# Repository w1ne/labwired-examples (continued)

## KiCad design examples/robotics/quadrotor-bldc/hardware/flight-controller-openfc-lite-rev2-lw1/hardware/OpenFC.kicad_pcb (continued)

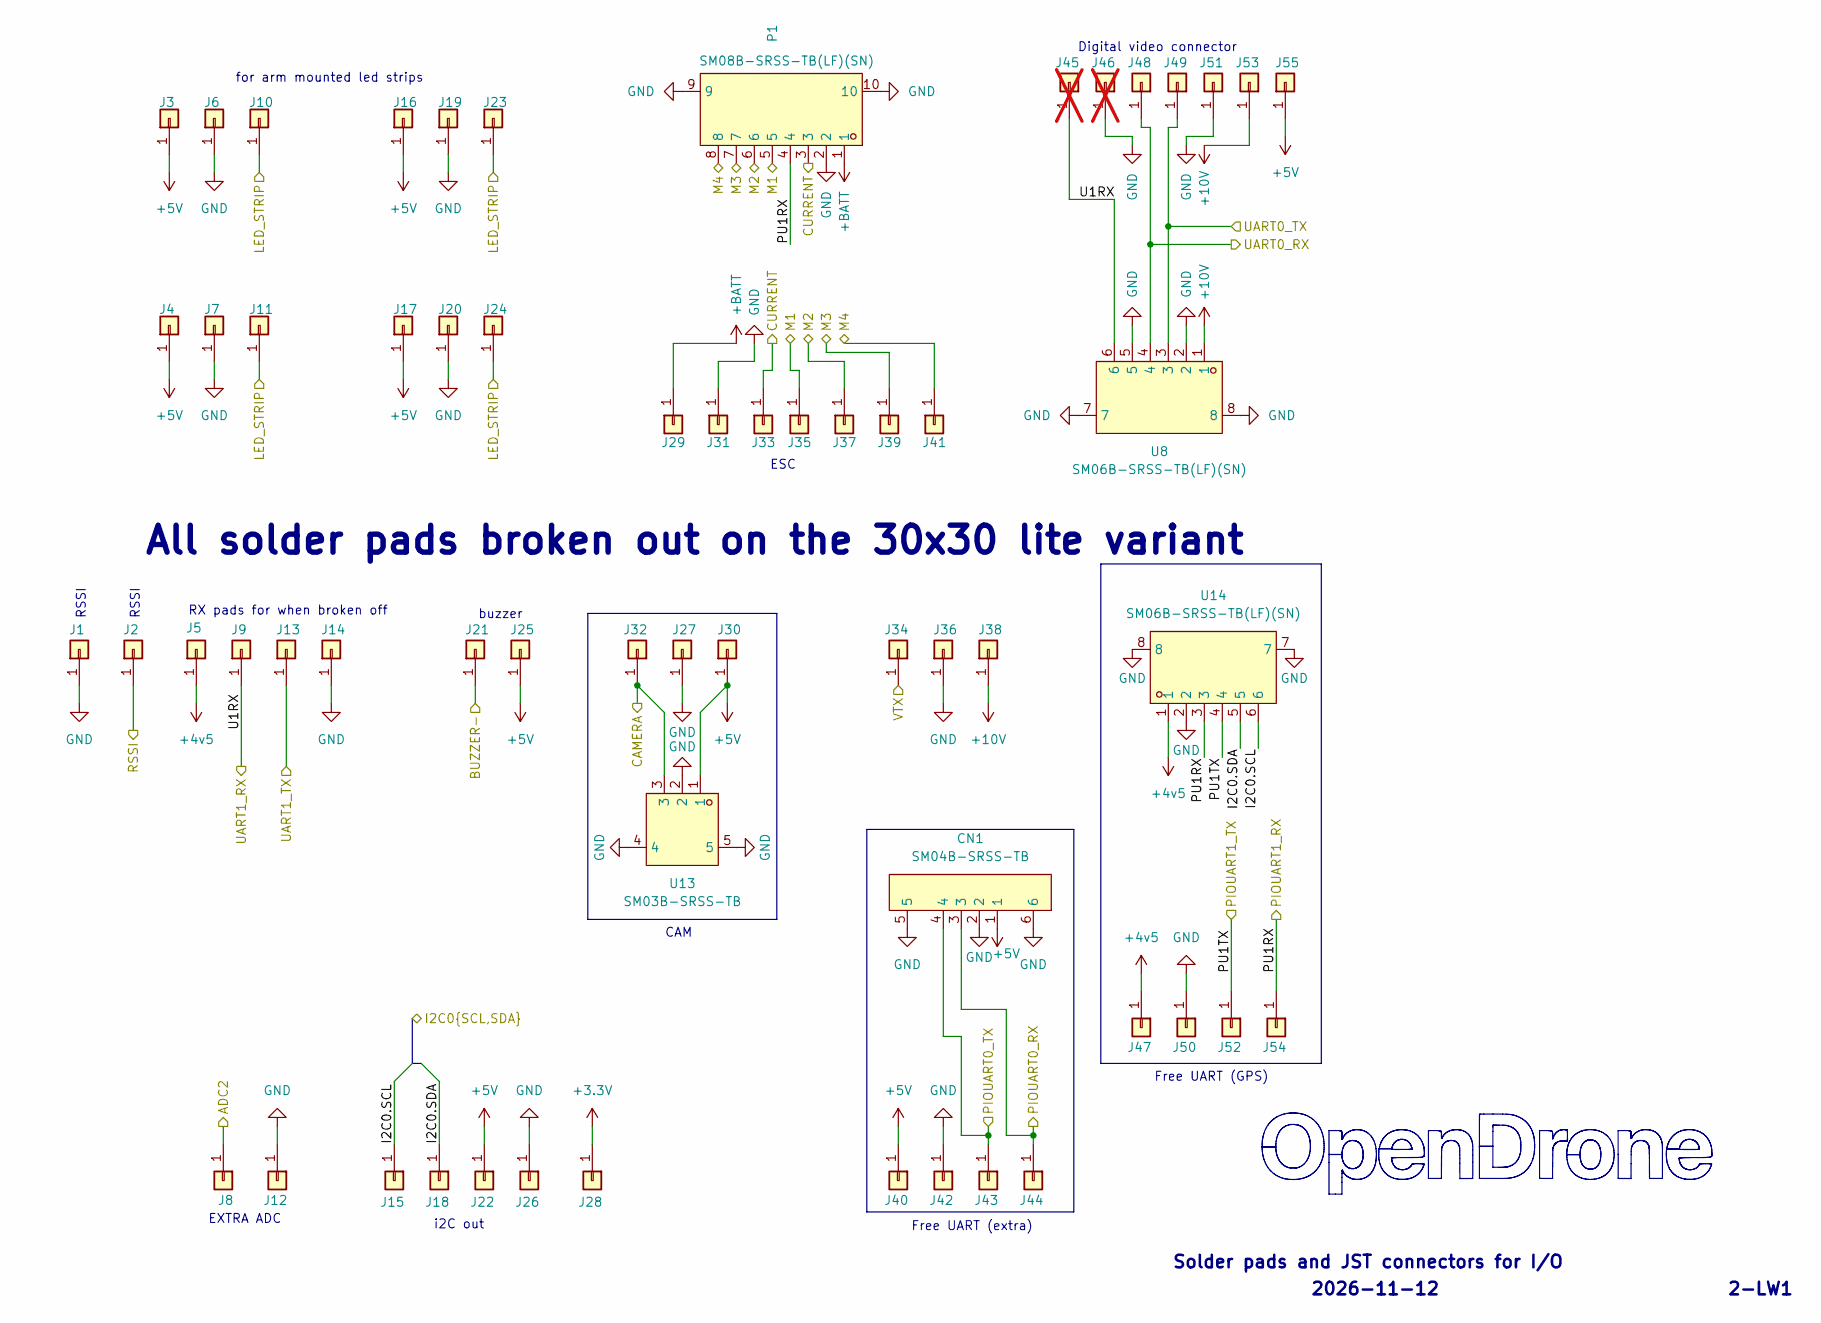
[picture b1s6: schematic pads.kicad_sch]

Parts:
CN1: SM04B-SRSS-TB; CONN-SMD_4P-P1.00_SM04B-SRSS-TB-LF-SN; MPN SM04B-SRSS-TB(LF)(SN); LCSC C160404
J1, J2, J3, J4, J5, J6, J7, J8, J9, J10, J11, J12, J13, J14, J15, J16, J17, J18, J19, J20, J21, J22, J23, J24, J25, J26, J27, J28, J29, J30, J31, J32, J33, J34, J35, J36, J37, J38, J39, J40, J41, J42, J43, J44, J47, J48, J49, J50, J51, J52, J53, J54, J55: 5V; small_pad
J45, J46: 5V; small_pad; not fitted
P1: SM08B-SRSS-TB(LF)(SN); CONN-TH_SM08B-SRSS-TB-LF-SN; MPN SM08B-SRSS-TB(LF)(SN); LCSC C160407
U8, U14: SM06B-SRSS-TB(LF)(SN); CONN-SMD_SM06B-SRSS-TB-LF-SN; MPN SM06B-SRSS-TB(LF)(SN); LCSC C160405
U13: SM03B-SRSS-TB; CONN-SMD_SM03B-SRSS-TB-LF-SN-P; MPN SM03B-SRSS-TB(LF)(SN); LCSC C160403

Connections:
+3.3V: J28.1 (Pin_1_1); also elsewhere on the board
+4v5: J5.1 (Pin_1_1), J47.1 (Pin_1_1), U14.1; also elsewhere on the board
+5V: CN1.1, J3.1 (Pin_1_1), J4.1 (Pin_1_1), J16.1 (Pin_1_1), J17.1 (Pin_1_1), J22.1 (Pin_1_1), J25.1 (Pin_1_1), J30.1 (Pin_1_1), J40.1 (Pin_1_1), J55.1 (Pin_1_1), U13.1; also elsewhere on the board
+10V: J38.1 (Pin_1_1), J53.1 (Pin_1_1), U8.1; also elsewhere on the board
+BATT: J29.1 (Pin_1_1), P1.1; also elsewhere on the board
/OSD/VIDEO_IN: J32.1 (Pin_1_1), U13.3; also elsewhere on the board
/OSD/VIDEO_OUT: J34.1 (Pin_1_1); also elsewhere on the board
/PADS/ADC2: J8.1 (Pin_1_1); also elsewhere on the board
/PADS/BUZZER-: J21.1 (Pin_1_1); also elsewhere on the board
/PADS/CURRENT: J33.1 (Pin_1_1), P1.3; also elsewhere on the board
/PADS/I2C0.SCL: J15.1 (Pin_1_1), U14.6; also elsewhere on the board
/PADS/I2C0.SDA: J18.1 (Pin_1_1), U14.5; also elsewhere on the board
/PADS/LED_STRIP: J10.1 (Pin_1_1), J11.1 (Pin_1_1), J23.1 (Pin_1_1), J24.1 (Pin_1_1); also elsewhere on the board
/PADS/M1: J35.1 (Pin_1_1), P1.5; also elsewhere on the board
/PADS/M2: J37.1 (Pin_1_1), P1.6; also elsewhere on the board
/PADS/M3: J39.1 (Pin_1_1), P1.7; also elsewhere on the board
/PADS/M4: J41.1 (Pin_1_1), P1.8; also elsewhere on the board
/PADS/PIOUART0_RX: CN1.3, J44.1 (Pin_1_1); also elsewhere on the board
/PADS/PIOUART0_TX: CN1.4, J43.1 (Pin_1_1); also elsewhere on the board
/PADS/PU1RX: J54.1 (Pin_1_1), P1.4, U14.3; also elsewhere on the board
/PADS/PU1TX: J52.1 (Pin_1_1), U14.4; also elsewhere on the board
/PADS/RSSI: J2.1 (Pin_1_1); also elsewhere on the board
/PADS/U1RX: J9.1 (Pin_1_1), J45.1, U8.6; also elsewhere on the board
/PADS/UART0_RX: J48.1 (Pin_1_1), U8.4; also elsewhere on the board
/PADS/UART0_TX: J49.1 (Pin_1_1), U8.3; also elsewhere on the board
/PADS/UART1_TX: J13.1 (Pin_1_1); also elsewhere on the board
GND: CN1.2, CN1.5, CN1.6, J1.1 (Pin_1_1), J6.1 (Pin_1_1), J7.1 (Pin_1_1), J12.1 (Pin_1_1), J14.1 (Pin_1_1), J19.1 (Pin_1_1), J20.1 (Pin_1_1), J26.1 (Pin_1_1), J27.1 (Pin_1_1), J31.1 (Pin_1_1), J36.1 (Pin_1_1), J42.1 (Pin_1_1), J46.1, J50.1 (Pin_1_1), J51.1 (Pin_1_1), P1.2, P1.9, P1.10, U8.2, U8.5, U8.7, U8.8, U13.2, U13.4, U13.5, U14.2, U14.7, U14.8; also elsewhere on the board

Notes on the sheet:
2026-11-12
RSSI
Free UART (extra)
Solder pads and JST connectors for I/O
i2C out
CAM
All solder pads broken out on the 30x30 lite variant
Free UART (GPS)
buzzer
2-LW1
RX pads for when broken off
ESC
Digital video connector
EXTRA ADC
for arm mounted led strips

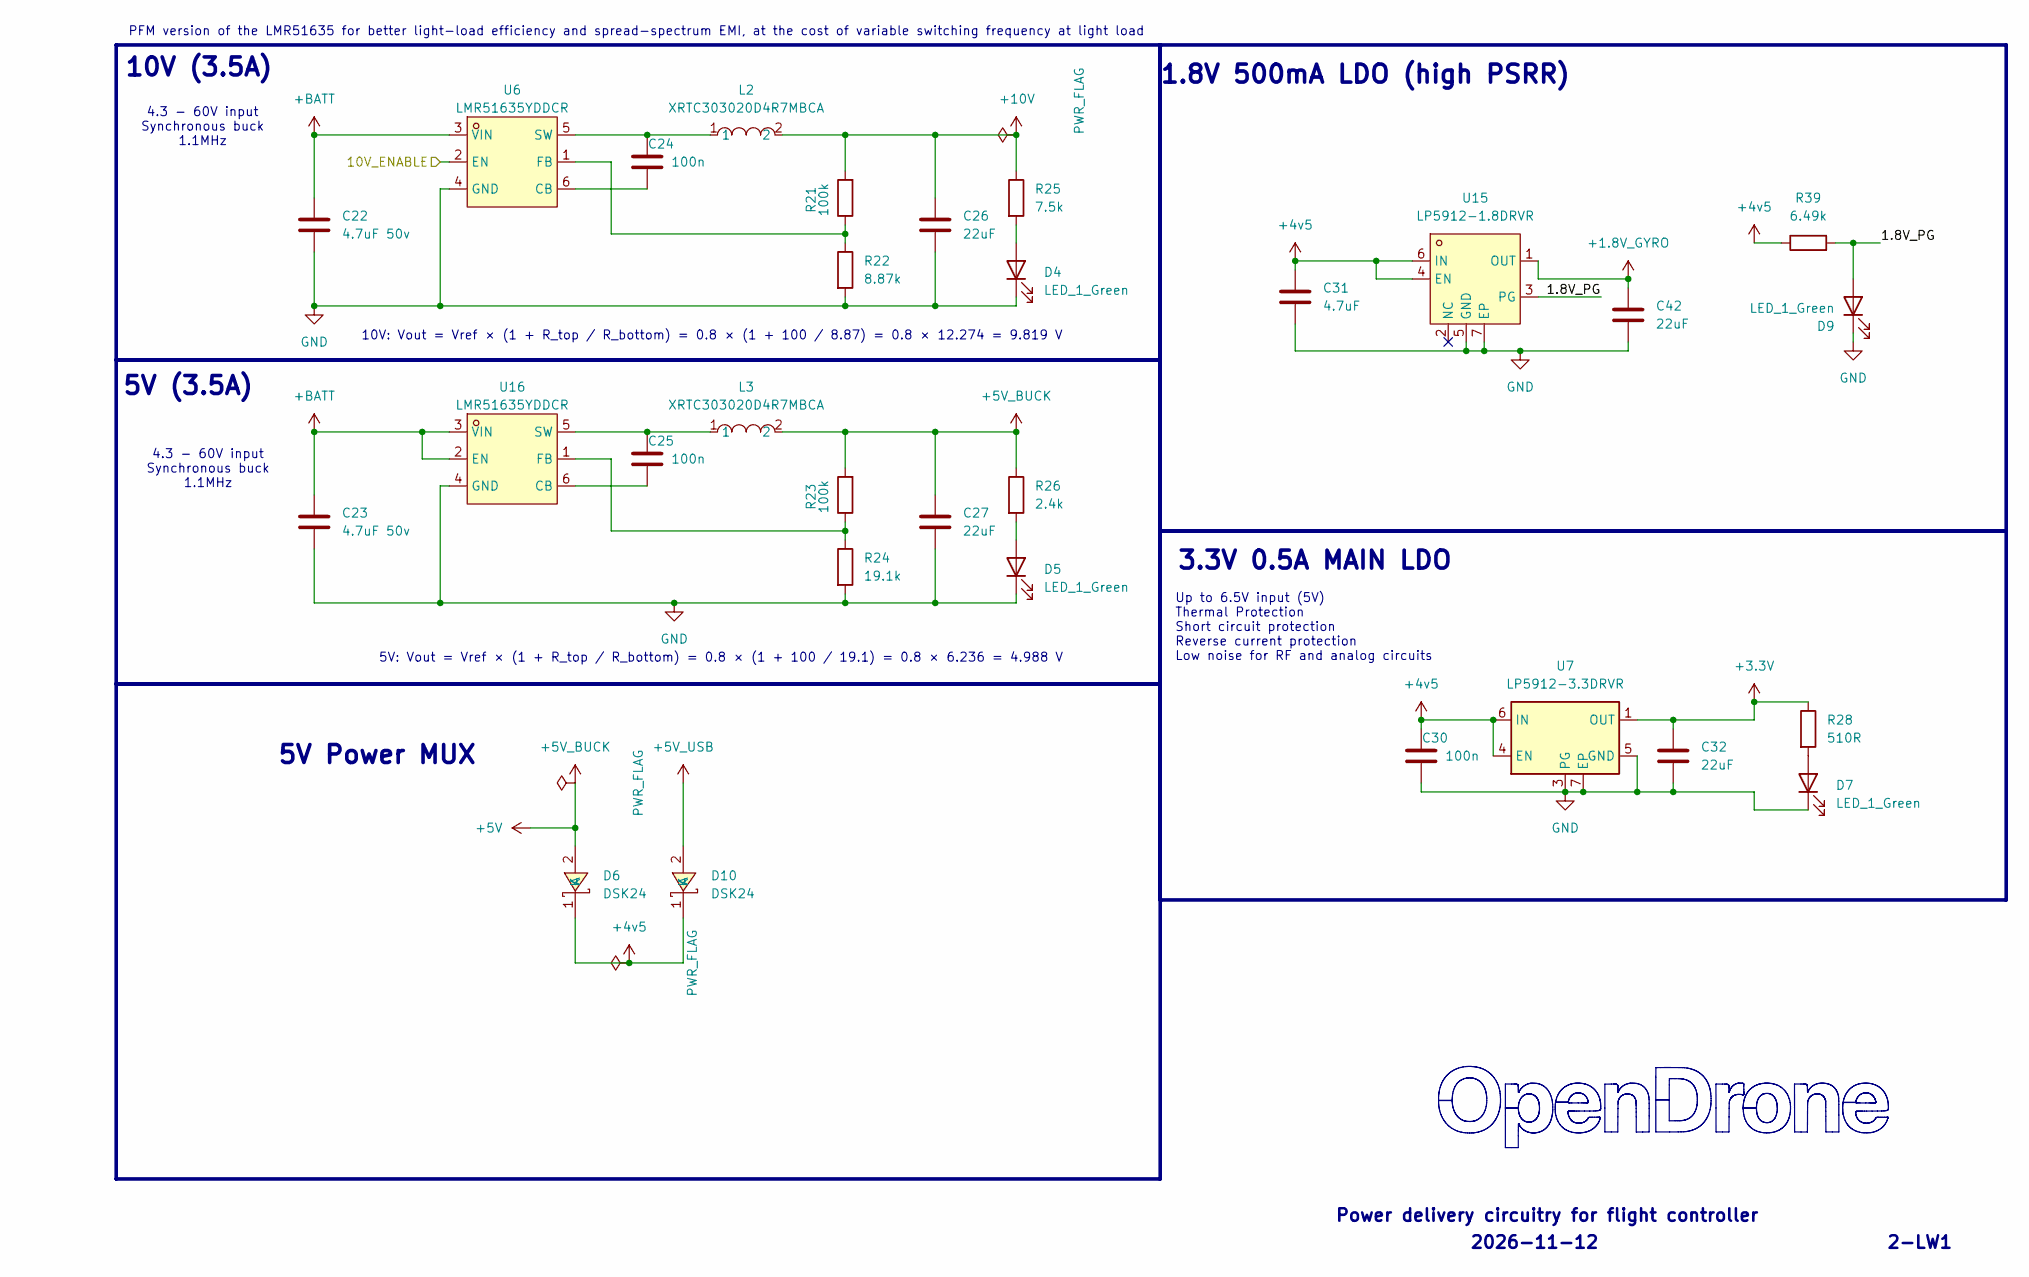
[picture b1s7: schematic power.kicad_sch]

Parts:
C22, C23: 4.7uF 50v; C_0805_2012Metric; MPN CL21A475KBQNNNE; LCSC C98192
C24, C25, C30: 100n; C_0201_0603Metric; MPN GRM033R61E104KE14D; LCSC C76939
C26, C27: 22uF; C_0603_1608Metric; MPN CL10A226MO7JZNC; LCSC C2762594
C31: 4.7uF; C_0402_1005Metric; MPN CL05A475MP5NRNC; LCSC C23733
C32: 22uF; C_0402_1005Metric; MPN CL05A226MQ5QUNC; LCSC C105226
C42: 22uF; C_0402_1005Metric; MPN GRM155R60J226ME11D; LCSC C415703
D4, D5, D7, D9: LED_1_Green; LED_0402_1005Metric; MPN XL-1005UGC; LCSC C965793
D6, D10: DSK24; SOD-123_L2.8-W1.8-LS3.7-RD; MPN DSK24; LCSC C64890
L2, L3: XRTC303020D4R7MBCA; IND-SMD_L3.0-W3.0_AFE303020S; MPN XRTC303020D4R7MBCA; LCSC C39846837
R21, R23: 100k; R_0201_0603Metric; MPN 0201WMF1003TEE; LCSC C270364
R22: 8.87k; R_0201_0603Metric; MPN RTT018871FTH; LCSC C332577
R24: 19.1k; R_0201_0603Metric; MPN RC-01W1912FT; LCSC C320741
R25: 7.5k; R_0201_0603Metric; MPN RC0201FR-077K5L; LCSC C474437
R26: 2.4k; R_0201_0603Metric; MPN RTT012401FTH; LCSC C166281
R28: 510R; R_0201_0603Metric; MPN RC0201FR-07510RL; LCSC C57784
R39: 6.49k; R_0201_0603Metric; MPN AF0201FR-076K49L; LCSC C2107920
U6, U16: LMR51635YDDCR; SOT-23-6_L2.9-W1.6-P0.95-LS2.8-BL; MPN LMR51635YDDCR; LCSC C45262770
U7: LP5912-3.3DRVR; WSON-6-1EP_2x2mm_P0.65mm_EP1x1.6mm; MPN LP5912-3.3DRVR; LCSC C524780
U15: LP5912-1.8DRVR; WSON-6-1EP_2x2mm_P0.65mm_EP1x1.6mm_ThermalVias; MPN LP5912-1.8DRVR; LCSC C2876234

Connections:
+1.8V_GYRO: C42.1, U15.1 (OUT); also elsewhere on the board
+3.3V: C32.1, R28.1, U7.1 (OUT); also elsewhere on the board
+4v5: C30.1, C31.1, D6.1 (K), D10.1 (K), R39.1, U7.4 (EN), U7.6 (IN), U15.4 (EN), U15.6 (IN); also elsewhere on the board
+5V: C27.1, D6.2 (A), L3.2, R23.2, R26.1; also elsewhere on the board
+5V_USB: D10.2 (A); also elsewhere on the board
+10V: C26.1, L2.2, R21.2, R25.1; also elsewhere on the board
+BATT: C22.1, C23.1, U6.3 (VIN), U16.2 (EN), U16.3 (VIN); also elsewhere on the board
/POWER/1.8V_PG: D9.2 (A), R39.2, U15.3 (PG)
/POWER/10V_ENABLE: U6.2 (EN); also elsewhere on the board
GND: C22.2, C23.2, C26.2, C27.2, C30.2, C31.2, C32.2, C42.2, D4.1 (K), D5.1 (K), D7.1 (K), D9.1 (K), R22.2, R24.2, U6.4 (GND), U7.3 (GND), U7.5 (PG), U7.7 (EP), U15.5 (GND), U15.7 (EP), U16.4 (GND); also elsewhere on the board
unnamed: D4.2 (A), R25.2
unnamed: D5.2 (A), R26.2
unnamed: D7.2 (A), R28.2
unnamed: C24.2, U6.6 (CB)
unnamed: R21.1, R22.1, U6.1 (FB)
unnamed: C24.1, L2.1, U6.5 (SW)
unnamed: C25.2, U16.6 (CB)
unnamed: R23.1, R24.1, U16.1 (FB)
unnamed: C25.1, L3.1, U16.5 (SW)

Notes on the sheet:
5V Power MUX
4.3 - 60V input Synchronous buck 1.1MHz
Power delivery circuitry for flight controller
2026-11-12
2-LW1
10V: Vout = Vref × (1 + R_top / R_bottom) = 0.8 × (1 + 100 / 8.87) = 0.8 × 12.274 = 9.819 V
5V: Vout = Vref × (1 + R_top / R_bottom) = 0.8 × (1 + 100 / 19.1) = 0.8 × 6.236 = 4.988 V
Up to 6.5V input (5V) Thermal Protection Short circuit protection Reverse current protection Low noise for RF and analog circuits
5V (3.5A)
1.8V 500mA LDO (high PSRR)
PFM version of the LMR51635 for better light-load efficiency and spread-spectrum EMI, at the cost of variable switching frequency at light load
10V (3.5A)
3.3V 0.5A MAIN LDO

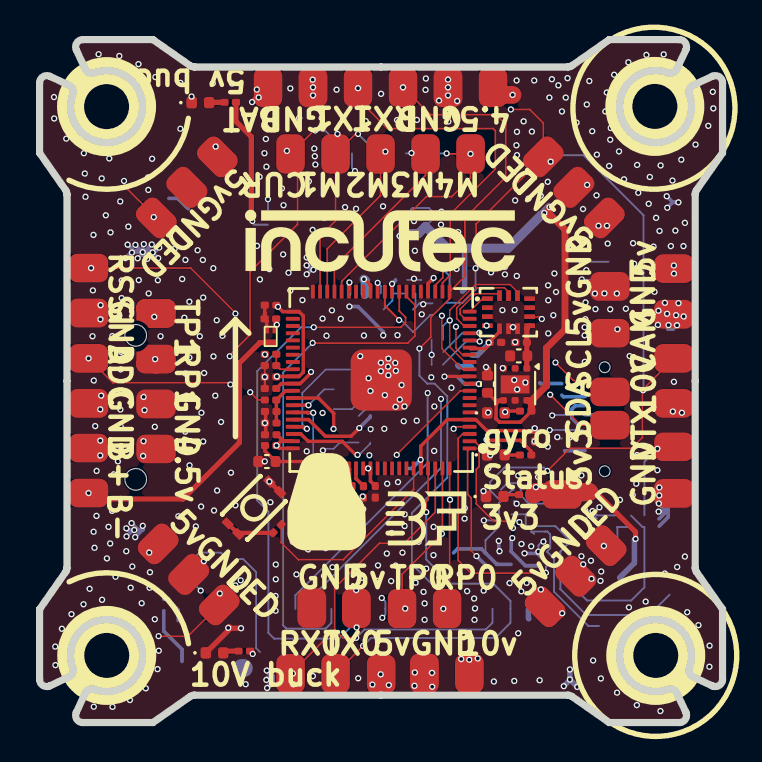
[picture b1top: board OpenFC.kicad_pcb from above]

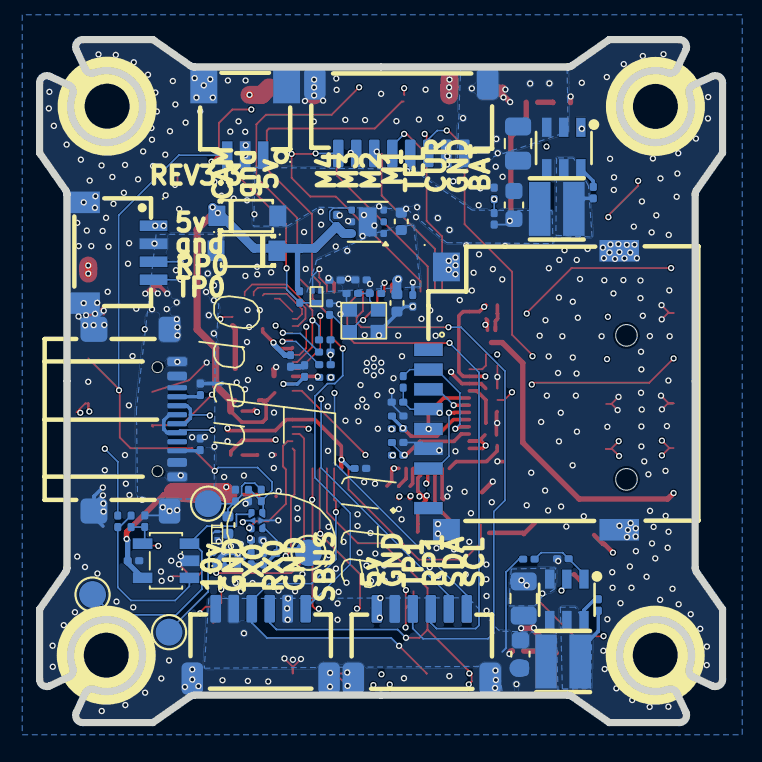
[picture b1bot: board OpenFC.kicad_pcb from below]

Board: 6 copper layers, 37.9 x 37.9 mm, 164 parts (72 on the bottom side), 82 nets.

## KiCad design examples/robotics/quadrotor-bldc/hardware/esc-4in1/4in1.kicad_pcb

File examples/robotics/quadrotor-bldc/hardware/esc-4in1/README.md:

# OpenESC quadrotor electrical and PCB source

The current KiCad 10 source passes native ERC, DRC and schematic-to-PCB parity.
This physical AT32F421/AM32 ESC remains separate from LabWired's runnable
STM32L476 reduced-order motor demonstration.

## Source and hardware

Derivative of [OpenDrone OpenESC-30x30](https://github.com/OpenDrone-hw/OpenESC-30x30),
commit `bf306934b5decc130ab1df6b653563ea16165e8e`, under CERN-OHL-S-2.0.
The manufacturer library is pinned at `fdf8319b3512925a7566532ae4b38a298cf54c24`.
Four AT32F421G8U7 MCUs drive four NSG2065Q gate drivers and 24 SP40N01GHNK
MOSFETs. The selected drone uses 4S LiPo: 14.8 V nominal, 16.8 V fully charged.
The PCB regulator rails are +10V and +3V3. A 24 V STM32 motor plant is not
the electrical equivalent of this hardware.

## Native results — 2026-11-11

| Check | Result |
|---|---:|
| Physical footprints | 222 |
| Physical pad objects | 1,067 |
| Populated SMT placements | 213 |
| Exact schematic nets | 210 |
| Track and via objects | 2,914 |
| Vias, including blind microvias | 1,716 |
| Blind In4.Cu to B.Cu microvias | 15 |
| KiCad 10.0.8 ERC errors / warnings | 0 / 0 |
| DRC findings / unconnected / schematic parity | 0 / 0 / 0 |

All 210 physical net memberships match the prior schematic exactly. No rule
severity was disabled. The reports list inherited ignored rule categories.

## Repairs

All 16 originally omitted physical MCU/driver pads are now present. The last
three U2 pads (8/23/24) are isolated from former overlapping copper through
four new blind microvias and In4.Cu routing. The prior 1,064-pad source still
omitted these three pads; the corrected source has 1,067 pads.

Local frozen source libraries provide 119 datasheet-backed pin-type corrections.
Capacitors and connectors no longer pretend to be input pins or power sources.
Thirty-one explicit power declarations represent the battery feed, buck output
after its inductor, filtered analog rails, internal bootstrap diodes and switched
phase references. They describe source paths; they do not validate voltage,
startup, bootstrap refresh or protection behavior. Two custom footprints are
frozen from their exact PCB shapes. The existing drawing uses a 25 mil connection
grid, and phase labels now match their hierarchical port names.

## Files and reproduction

- `4in1.kicad_sch`, `ESC.kicad_sch`: complete five-sheet electrical source.
- `4in1.kicad_pcb`, `.kicad_pro`, `.kicad_dru`: native routed board and rules.
- `reviewed-symbols/`, `reviewed-footprints.pretty/`: local source libraries.
- `reviewed-models/`: official KiCad package models, pinned hashes and license.
- [Native review](validation/README.md), [ERC](validation/erc-final.txt),
  [DRC](validation/drc-final.txt), [netlist comparison](validation/20261111/netlist-equivalence.json).
- [Hosted import coverage](validation/20261111/labwired-import-coverage.json).
- `fabrication-review/esc-board-populated.step` and `.glb`: actual populated board.

Run `bash validation/run_native_checks.sh`. It uses `kicad/kicad:10.0` and fails
if ERC, DRC or parity report a finding. Review exports are not an order.

## Remaining limits

The generic LabWired import preserves all 222 components and 210 nets with zero
dropped pin endpoints. It maps 176 passive parts and keeps 46 inert parts.
The actual MCU, driver, MOSFET, regulator and current-amplifier models remain
unsupported: `design_only`, `twin_buildable: false`. The actual AM32 power stage,
battery sag, MOSFET switching, thermal behavior and aircraft flight are untested.

The factory must review the six-layer process, 15 blind microvias, via-in-pad,
trace current density and analog return paths. First-article electrical and
thermal validation remains outstanding. Do not order or power this review-only
board based solely on ERC/DRC.

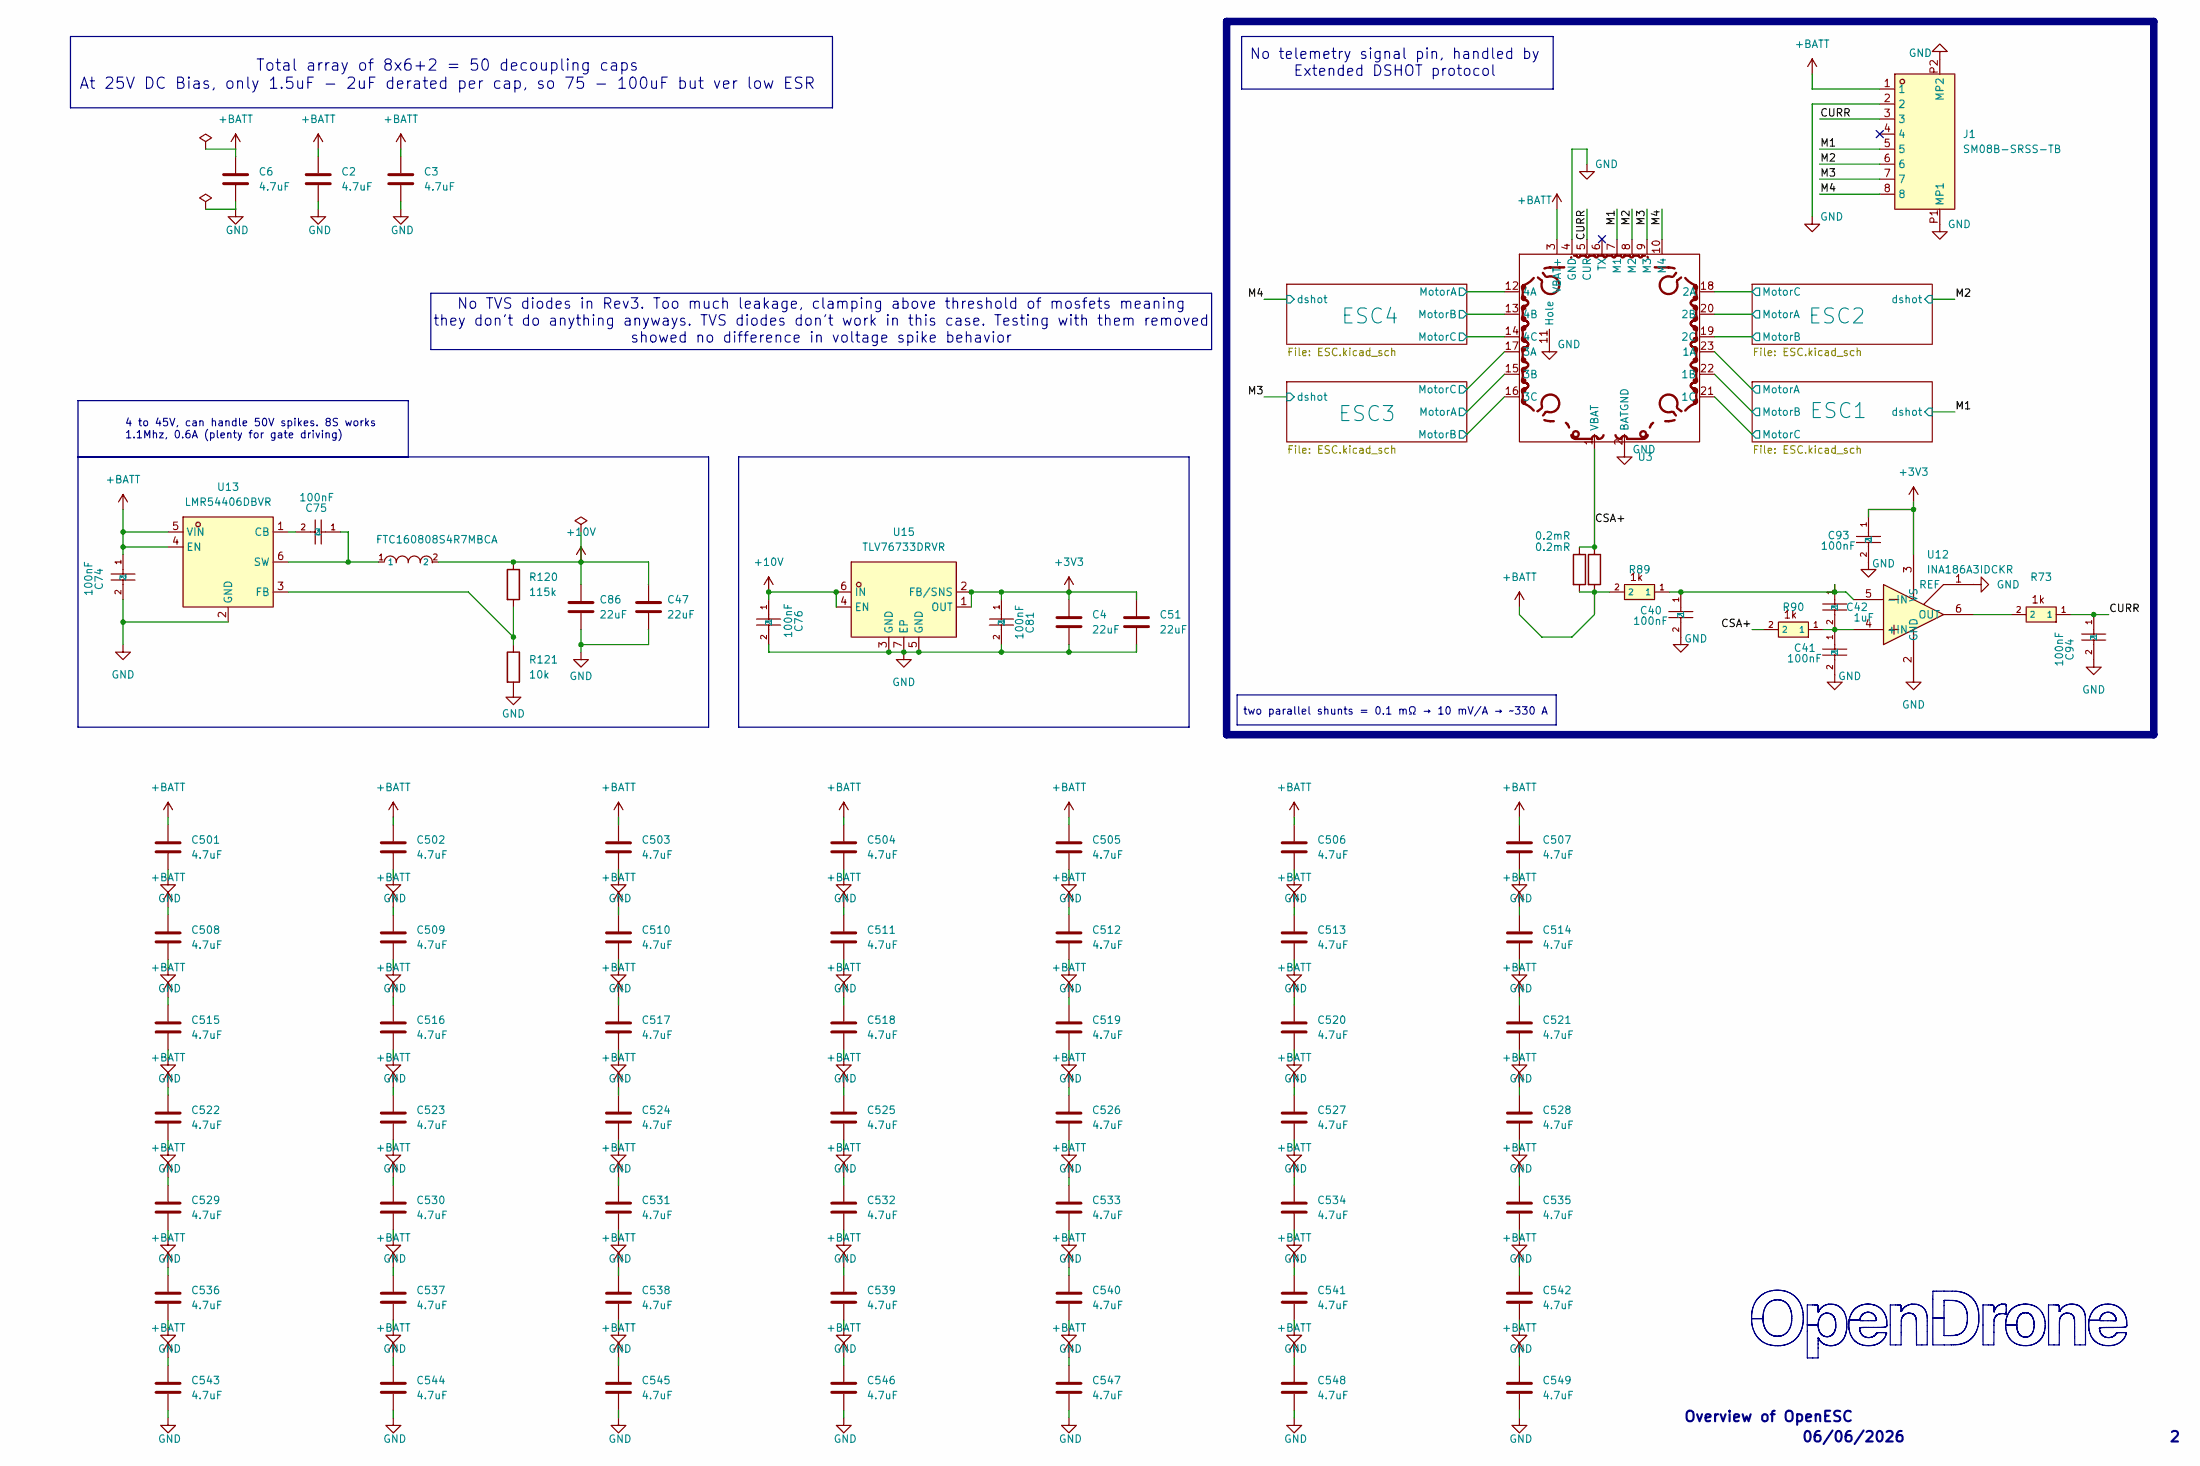
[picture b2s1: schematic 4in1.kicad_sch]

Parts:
C2, C3, C6, C501, C502, C503, C504, C505, C506, C507, C508, C509, C510, C511, C512, C513, C514, C515, C516, C517, C518, C519, C520, C521, C522, C523, C524, C525, C526, C527, C528, C529, C530, C531, C532, C533, C534, C535, C536, C537, C538, C539, C540, C541, C542, C543, C544, C545, C546, C547, C548, C549: 4.7uF; C_1206_3216Metric; MPN TCC1206X7R475K500HT; LCSC C380366
C4, C51: 22uF; C_0402_1005Metric; MPN CL05A226MQ5QUNC; LCSC C105226
C40, C41: 100nF; C_0402_WIDE; MPN CL05B104KB54PNC; LCSC C307331
C42: 1uF; C_0402_1005Metric; MPN CC0402KRX7R6BB105; LCSC C7500381
C47, C86: 22uF; C_0603_1608Metric; MPN CL10A226MO7JZNC; LCSC C2762594
C74, C75, C76, C81, C93, C94: 100nF; C_0201_0603Metric; MPN GRM033R6YA104KE14D; LCSC C181043
J1: SM08B-SRSS-TB; JST_SM08B-SRSS-TB; MPN SM08B-SRSS-TB(LF)(SN); LCSC C160407
R73, R89, R90: 1k; C_0201_0603Metric; MPN 0201WMF1001TEE; LCSC C270365
R120: 115k; R_0201_0603Metric; MPN RTT011153FTH; LCSC C166378
R121: 10k; R_0201_0603Metric; MPN RC0201FR-0710KL; LCSC C106225
Rsense1, Rsense2: 0.2mR; R_2512_6332Metric; MPN ASR-S-3-0.2F; LCSC C695806
U3: 4in1ESC30x30
U12: INA186A3IDCKR; SOT-363_SC-70-6; MPN INA186A3IDCKR; LCSC C2058245
U13: LMR54406DBVR; SOT-23-6_L2.9-W1.6-P0.95-LS2.8-BR; MPN LMR54406DBVR; LCSC Part C5219316
U14: FTC160808S4R7MBCA; IND-SMD_L1.6-W0.8_FTC160865SR47MBCA; MPN FTC160808S4R7MBCA; LCSC C46594347
U15: TLV76733DRVR; WSON-6_L2.0-W2.0-P0.65-TL-EP; MPN TLV76733DRVR; LCSC C2848334

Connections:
+3V3: C4.2, C51.2, C81.1, C93.1, U12.3 (VS), U15.1 (OUT), U15.2 (FB/SNS); also elsewhere on the board
+10V: C47.1, C76.1, C86.1, R120.1, U14.2, U15.4 (EN), U15.6 (IN); also elsewhere on the board
+BATT: C2.1, C3.1, C6.1, C74.1, C501.1, C502.1, C503.1, C504.1, C505.1, C506.1, C507.1, C508.1, C509.1, C510.1, C511.1, C512.1, C513.1, C514.1, C515.1, C516.1, C517.1, C518.1, C519.1, C520.1, C521.1, C522.1, C523.1, C524.1, C525.1, C526.1, C527.1, C528.1, C529.1, C530.1, C531.1, C532.1, C533.1, C534.1, C535.1, C536.1, C537.1, C538.1, C539.1, C540.1, C541.1, C542.1, C543.1, C544.1, C545.1, C546.1, C547.1, C548.1, C549.1, J1.1, R89.2, Rsense1.2, Rsense2.2, U3.3 (VBAT+), U13.4 (EN), U13.5 (VIN); also elsewhere on the board
/CSA+: R90.2, Rsense1.1, Rsense2.1, U3.1 (VBAT)
/CURR: C94.1, J1.3, R73.1, U3.5 (CUR)
/ESC1/MotorA: U3.23 (1A); also elsewhere on the board
/ESC1/MotorB: U3.22 (1B); also elsewhere on the board
/ESC1/MotorC: U3.21 (1C); also elsewhere on the board
/ESC2/MotorA: U3.20 (2B); also elsewhere on the board
/ESC2/MotorB: U3.19 (2C); also elsewhere on the board
/ESC2/MotorC: U3.18 (2A); also elsewhere on the board
/ESC3/MotorA: U3.15 (3B); also elsewhere on the board
/ESC3/MotorB: U3.16 (3C); also elsewhere on the board
/ESC3/MotorC: U3.17 (3A); also elsewhere on the board
/ESC4/MotorA: U3.12 (4A); also elsewhere on the board
/ESC4/MotorB: U3.13 (4B); also elsewhere on the board
/ESC4/MotorC: U3.14 (4C); also elsewhere on the board
/M1: J1.5, U3.7 (M1); also elsewhere on the board
/M2: J1.6, U3.8 (M2); also elsewhere on the board
/M3: J1.7, U3.9 (M3); also elsewhere on the board
/M4: J1.8, U3.10 (M4); also elsewhere on the board
GND: C2.2, C3.2, C4.1, C6.2, C40.2, C41.2, C47.2, C51.1, C74.2, C76.2, C81.2, C86.2, C93.2, C94.2, C501.2, C502.2, C503.2, C504.2, C505.2, C506.2, C507.2, C508.2, C509.2, C510.2, C511.2, C512.2, C513.2, C514.2, C515.2, C516.2, C517.2, C518.2, C519.2, C520.2, C521.2, C522.2, C523.2, C524.2, C525.2, C526.2, C527.2, C528.2, C529.2, C530.2, C531.2, C532.2, C533.2, C534.2, C535.2, C536.2, C537.2, C538.2, C539.2, C540.2, C541.2, C542.2, C543.2, C544.2, C545.2, C546.2, C547.2, C548.2, C549.2, J1.2, J1.P1 (MP1), J1.P2 (MP2), R121.2, U3.2 (BATGND), U3.4 (GND), U3.11 (Hole), U12.1 (REF), U12.2 (GND), U13.2 (GND), U15.3 (GND), U15.5 (GND), U15.7 (EP); also elsewhere on the board
unnamed: C41.1, C42.2, R90.1, U12.4 (+IN)
unnamed: C40.1, C42.1, R89.1, U12.5 (-IN)
unnamed: R73.2, U12.6 (OUT)
unnamed: C75.2, U13.1 (CB)
unnamed: R120.2, R121.1, U13.3 (FB)
unnamed: C75.1, U13.6 (SW), U14.1

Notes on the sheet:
No telemetry signal pin, handled by Extended DSHOT protocol
Overview of OpenESC
No TVS diodes in Rev3. Too much leakage, clamping above threshold of mosfets meaning they don't do anything anyways. TVS diodes don't work in this case. Testing with them removed showed no difference in voltage spike behavior
06/06/2026
Total array of 8x6+2 = 50 decoupling caps At 25V DC Bias, only 1.5uF - 2uF derated per cap, so 75 - 100uF but ver low ESR
two parallel shunts = 0.1 mΩ → 10 mV/A → ~330 A
4 to 45V, can handle 50V spikes. 8S works 1.1Mhz, 0.6A (plenty for gate driving)
